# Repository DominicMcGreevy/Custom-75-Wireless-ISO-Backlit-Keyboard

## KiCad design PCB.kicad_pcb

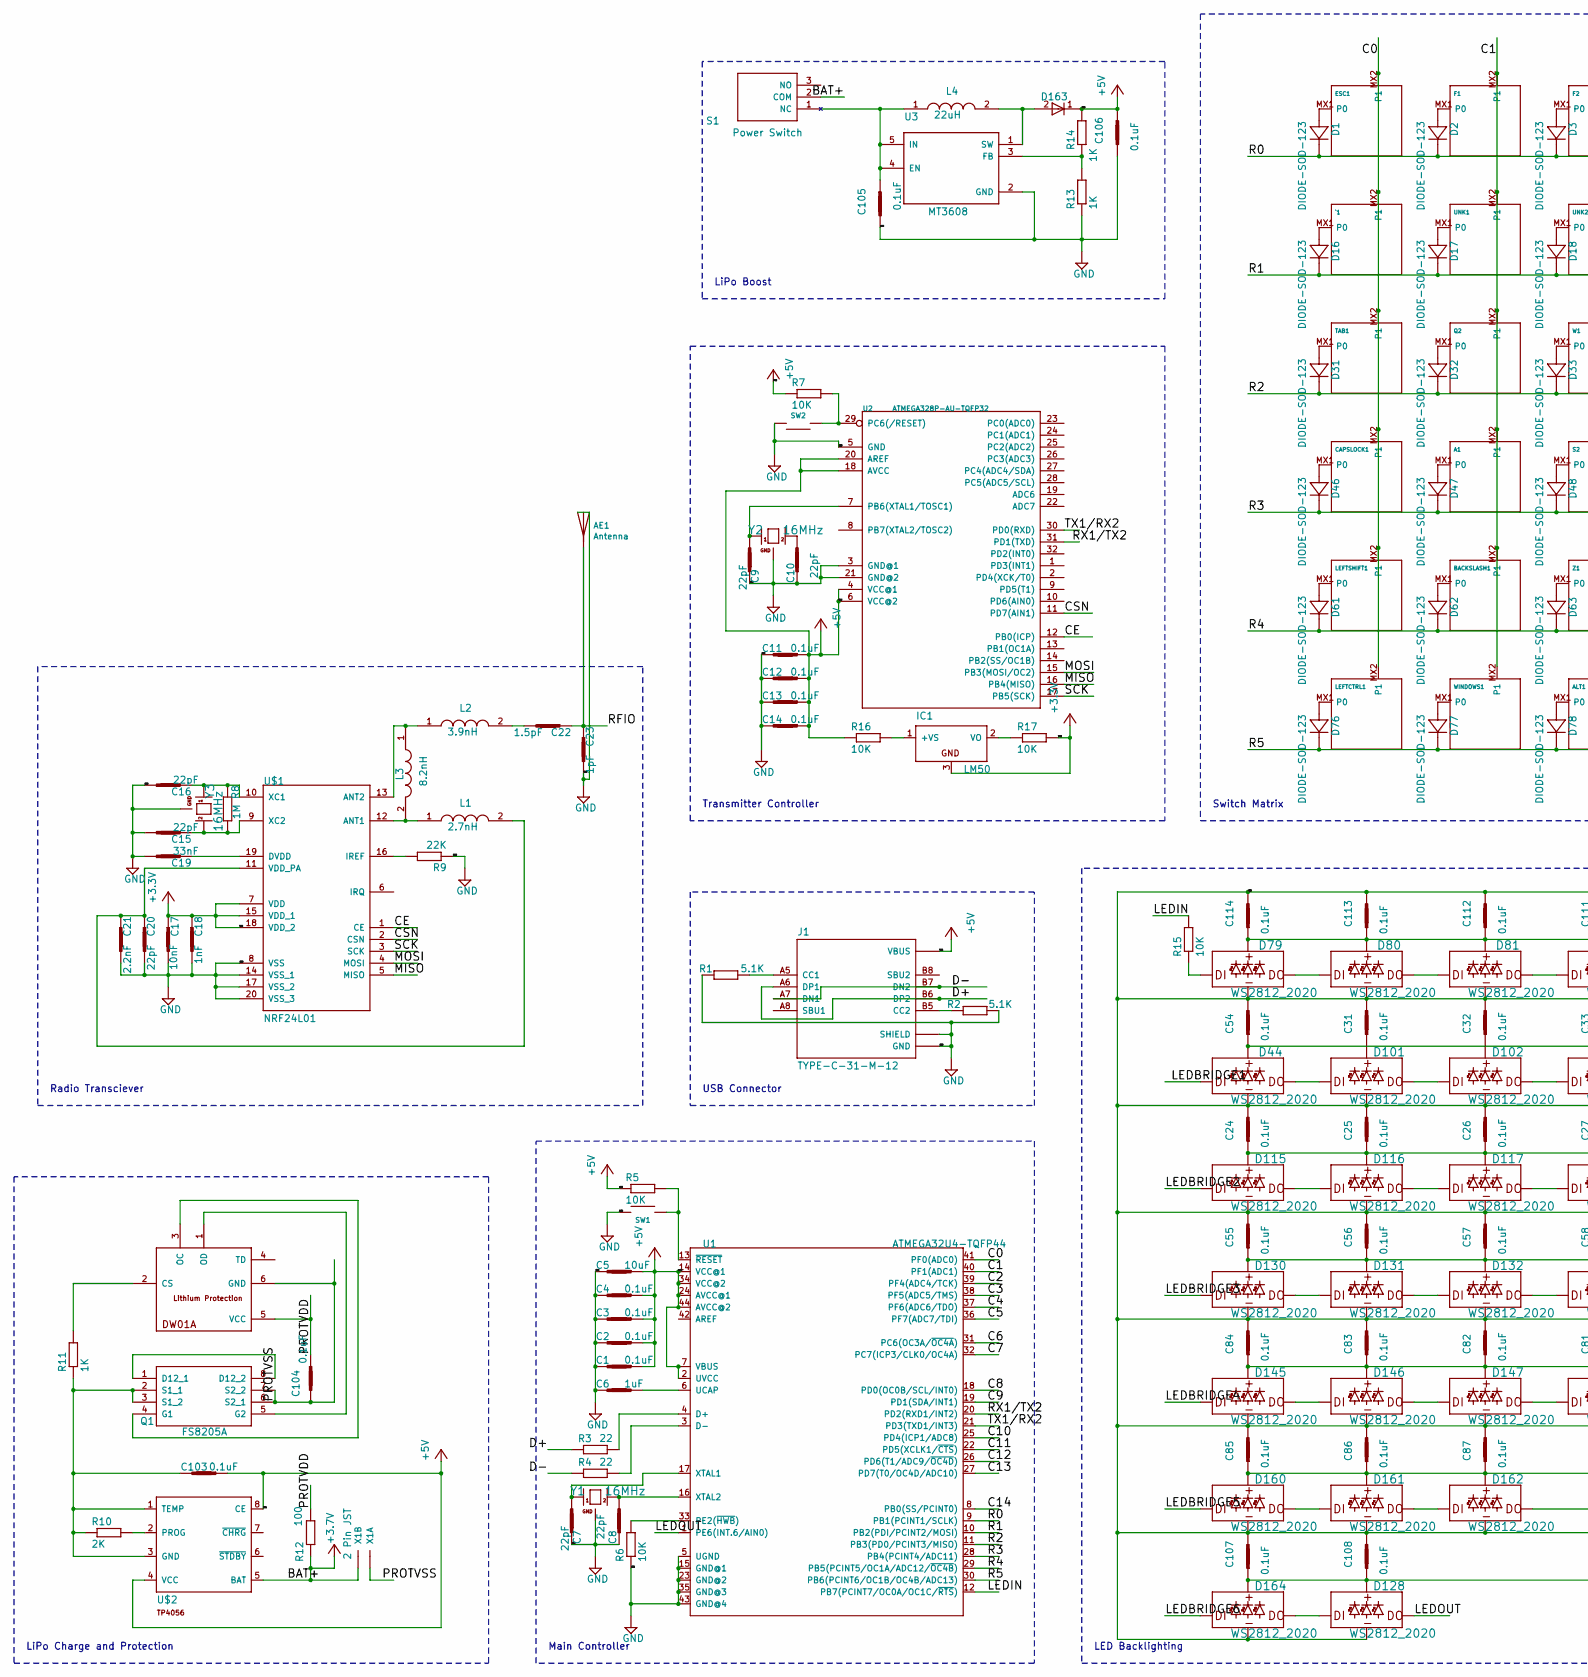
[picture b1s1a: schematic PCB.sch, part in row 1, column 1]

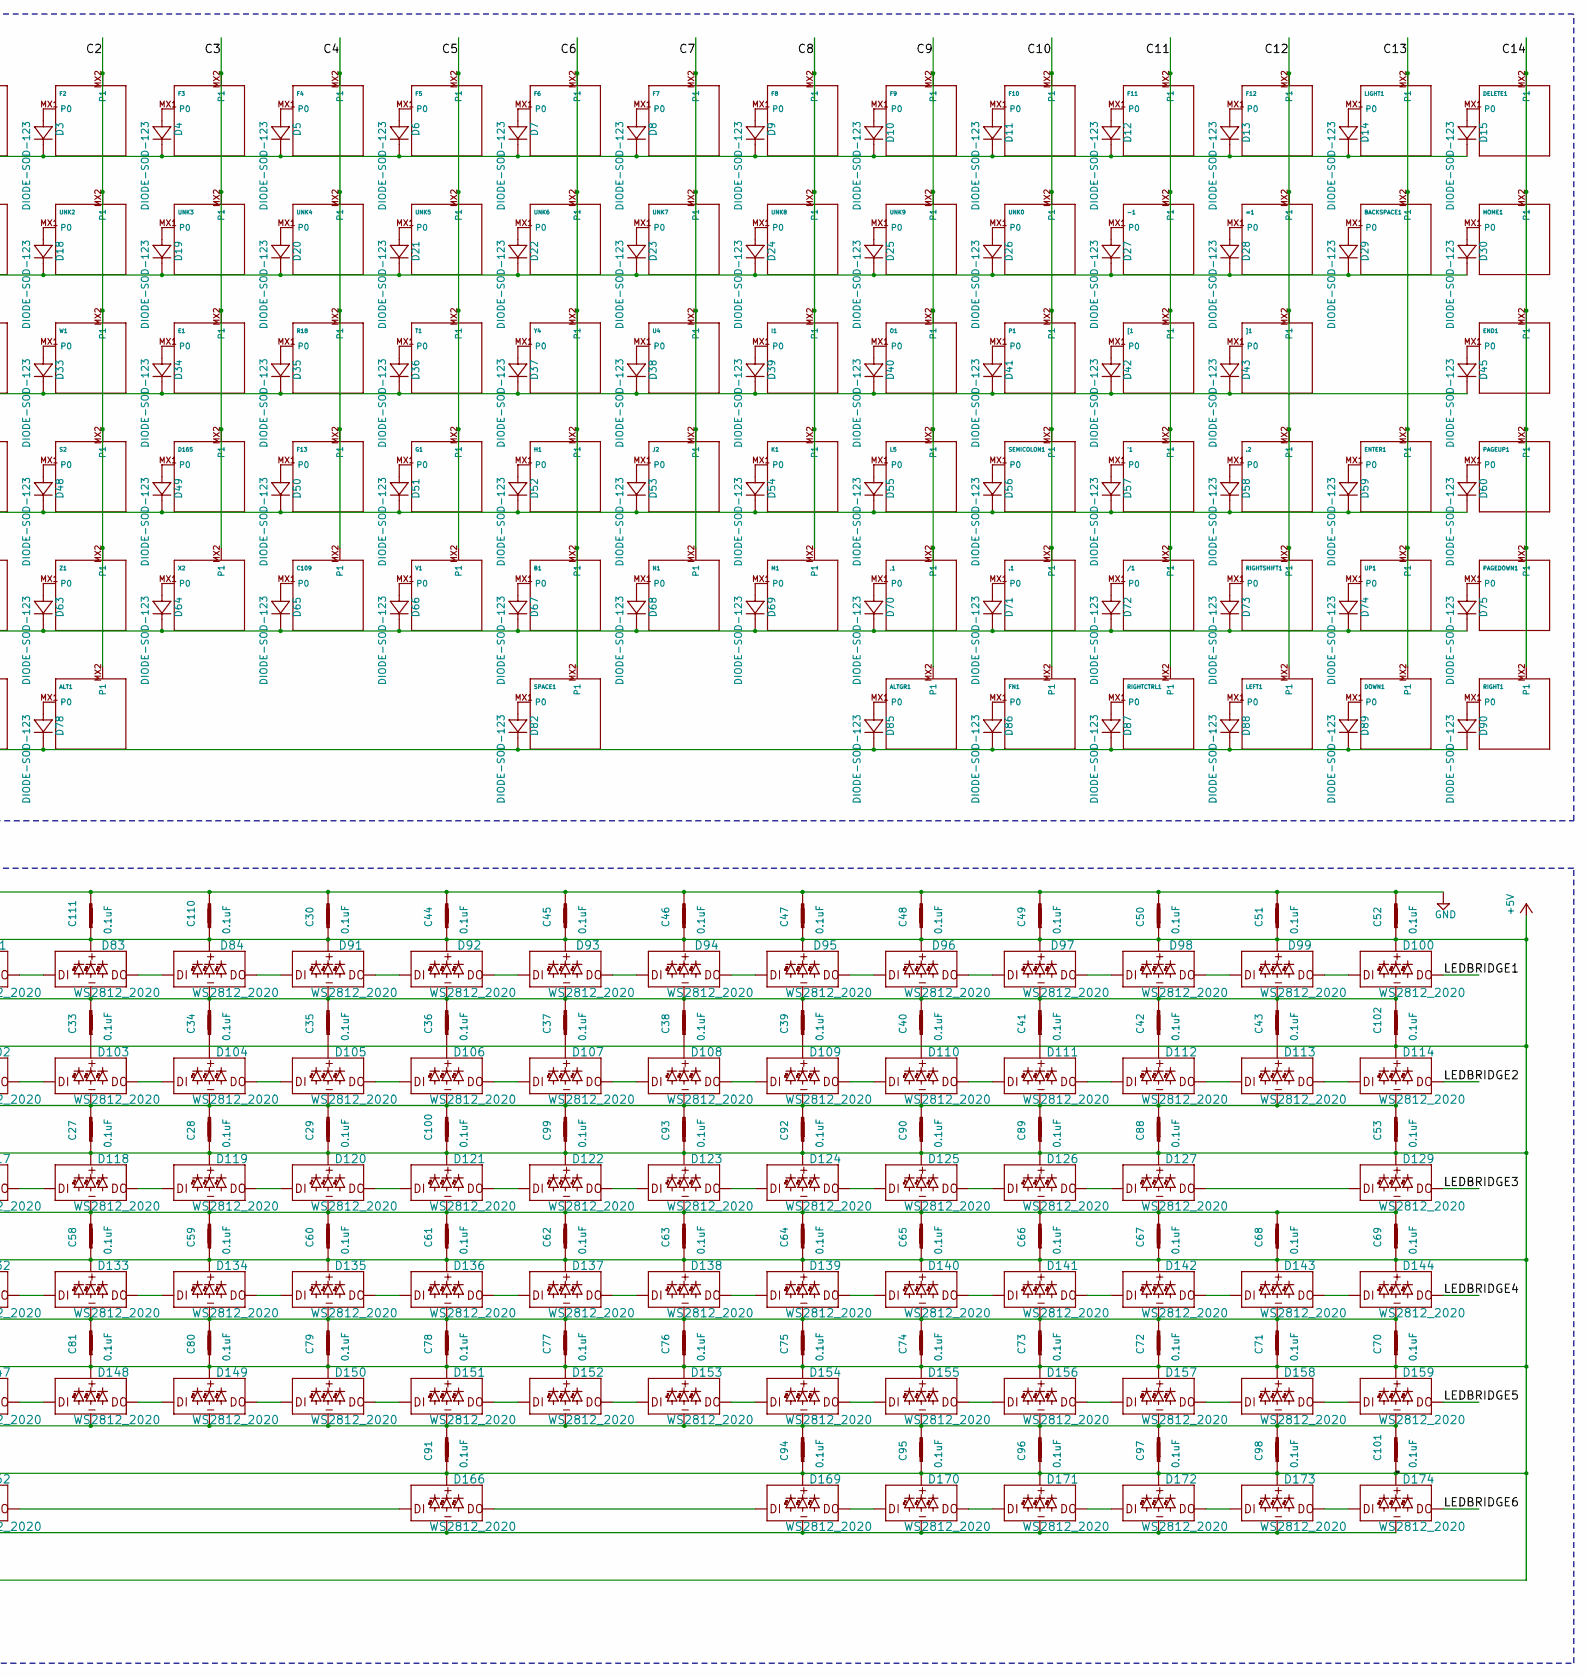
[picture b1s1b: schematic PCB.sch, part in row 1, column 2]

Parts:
'1: KEYSWITCH-PLAIN-MX-1U; MX-1U
,1: KEYSWITCH-PLAIN-MX-1U; MX-1U
-1: KEYSWITCH-PLAIN-MX-1U; MX-1U
.1, .2: KEYSWITCH-PLAIN-MX-1U; MX-1U
/1: KEYSWITCH-PLAIN-MX-1U; MX-1U
=1: KEYSWITCH-PLAIN-MX-1U; MX-1U
A1: KEYSWITCH-PLAIN-MX-1U; MX-1U
AE1: Antenna; Texas_SWRA117D_2.4GHz_Right
ALT1: KEYSWITCH-PLAIN-MX-1U; MX-1U
ALTGR1: KEYSWITCH-PLAIN-MX-1U; MX-1U
B1: KEYSWITCH-PLAIN-MX-1U; MX-1U
BACKSLASH1: KEYSWITCH-PLAIN-MX-1U; MX-1U
BACKSPACE1: KEYSWITCH-PLAIN-MX-2U-FLIPPED; MX-2U-FLIPPED
C1, C2, C3, C4, C11, C12, C13, C14, C24, C25, C26, C27, C28, C29, C30, C31, C32, C33, C34, C35, C36, C37, C38, C39, C40, C41, C42, C43, C44, C45, C46, C47, C48, C49, C50, C51, C52, C53, C54, C55, C56, C57, C58, C59, C60, C61, C62, C63, C64, C65, C66, C67, C68, C69, C70, C71, C72, C73, C74, C75, C76, C77, C78, C79, C80, C81, C82, C83, C84, C85, C86, C87, C88, C89, C90, C91, C92, C93, C94, C95, C96, C97, C98, C99, C100, C101, C102, C103, C104, C105, C106, C107, C108, C110, C111, C112, C113, C114: 0.1uF; C0805
C5: 10uF; C0805
C6: 1uF; C0805
C7, C8, C9, C10, C15, C16, C20: 22pF; C0805
C17: 10nF; C0805
C18: 1nF; C0805
C19: 33nF; C0805
C21: 2.2nF; C0805
C22: 1.5pF; C0805
C23: 1pF; C0805
C109: KEYSWITCH-PLAIN-MX-1U; MX-1U
CAPSLOCK1: KEYSWITCH-PLAIN-MX-1U; MX-1U
D1, D2, D3, D4, D5, D6, D7, D8, D9, D10, D11, D12, D13, D14, D15, D16, D17, D18, D19, D20, D21, D22, D23, D24, D25, D26, D27, D28, D29, D30, D31, D32, D33, D34, D35, D36, D37, D38, D39, D40, D41, D42, D43, D45, D46, D47, D48, D49, D50, D51, D52, D53, D54, D55, D56, D57, D58, D59, D60, D61, D62, D63, D64, D65, D66, D67, D68, D69, D70, D71, D72, D73, D74, D75, D76, D77, D78, D82, D85, D86, D87, D88, D89, D90: DIODE-SOD-123; SOD-123
D44, D79, D80, D81, D83, D84, D91, D92, D93, D94, D95, D96, D97, D98, D99, D100, D101, D102, D103, D104, D105, D106, D107, D108, D109, D110, D111, D112, D113, D114, D115, D116, D117, D118, D119, D120, D121, D122, D123, D124, D125, D126, D127, D128, D129, D130, D131, D132, D133, D134, D135, D136, D137, D138, D139, D140, D141, D142, D143, D144, D145, D146, D147, D148, D149, D150, D151, D152, D153, D154, D155, D156, D157, D158, D159, D160, D161, D162, D164, D166, D169, D170, D171, D172, D173, D174: WS2812_2020; WS2812-2020
D163: ES1D; DIOM5027-221N
D165: KEYSWITCH-PLAIN-MX-1U; MX-1U
DELETE1: KEYSWITCH-PLAIN-MX-1U; MX-1U
DOWN1: KEYSWITCH-PLAIN-MX-1U; MX-1U
E1: KEYSWITCH-PLAIN-MX-1U; MX-1U
END1: KEYSWITCH-PLAIN-MX-1U; MX-1U
ENTER1: KEYSWITCH-PLAIN-MX-2U-FLIPPED-ROTATED; MX-2U-FLIPPED-ROTATED
ESC1: KEYSWITCH-PLAIN-MX-1U; MX-1U
F1, F2, F3, F4, F5, F6, F7, F8, F9, F10, F11, F12, F13: KEYSWITCH-PLAIN-MX-1U; MX-1U
FN1: KEYSWITCH-PLAIN-MX-1U; MX-1U
G1: KEYSWITCH-PLAIN-MX-1U; MX-1U
H1: KEYSWITCH-PLAIN-MX-1U; MX-1U
HOME1: KEYSWITCH-PLAIN-MX-1U; MX-1U
I1: KEYSWITCH-PLAIN-MX-1U; MX-1U
IC1: LM50; SOT23
J1: TYPE-C-31-M-12; HRO_TYPE-C-31-M-12
J2: KEYSWITCH-PLAIN-MX-1U; MX-1U
K1: KEYSWITCH-PLAIN-MX-1U; MX-1U
L1: 2.7nH; LQW2BAN11NG00L
L2: 3.9nH; LQW18AS10NG0CD
L3: 8.2nH; LQW2BAN11NG00L
L4: 22uH; 7447706220
L5: KEYSWITCH-PLAIN-MX-1U; MX-1U
LEFT1: KEYSWITCH-PLAIN-MX-1U; MX-1U
LEFTCTRL1: KEYSWITCH-PLAIN-MX-1U; MX-1U
LEFTSHIFT1: KEYSWITCH-PLAIN-MX-1U; MX-1U
LIGHT1: KEYSWITCH-PLAIN-MX-1U; MX-1U
M1: KEYSWITCH-PLAIN-MX-1U; MX-1U
N1: KEYSWITCH-PLAIN-MX-1U; MX-1U
O1: KEYSWITCH-PLAIN-MX-1U; MX-1U
P1: KEYSWITCH-PLAIN-MX-1U; MX-1U
PAGEDOWN1: KEYSWITCH-PLAIN-MX-1U; MX-1U
PAGEUP1: KEYSWITCH-PLAIN-MX-1U; MX-1U
Q1: FS8205A; SOP65P640X120-8N
Q2: KEYSWITCH-PLAIN-MX-1U; MX-1U
R1, R2: 5.1K; R0805
R3, R4: 22; R0805
R5, R6, R7, R15, R16, R17: 10K; R0805
R8: 1M; R0805
R9: 22K; R0805
R10: 2K; R0805
R11, R13, R14: 1K; R0805
R12: 100; R0805
R18: KEYSWITCH-PLAIN-MX-1U; MX-1U
RIGHT1: KEYSWITCH-PLAIN-MX-1U; MX-1U
RIGHTCTRL1: KEYSWITCH-PLAIN-MX-1U; MX-1U
RIGHTSHIFT1: KEYSWITCH-PLAIN-MX-1U; MX-1U
S1: Power Switch; MINISPDTSW
S2: KEYSWITCH-PLAIN-MX-1U; MX-1U
SEMICOLON1: KEYSWITCH-PLAIN-MX-1U; MX-1U
SPACE1: KEYSWITCH-PLAIN-MX-6.25U-FLIPPED; MX-6.25U-FLIPPED
SW1, SW2: SWITCH-SMD-EVP-BB2A9B00
T1: KEYSWITCH-PLAIN-MX-1U; MX-1U
TAB1: KEYSWITCH-PLAIN-MX-1U; MX-1U
U1: ATMEGA32U4-TQFP44; TQFP44-0.8-9.6X9.6MM
U2: ATMEGA328P-AU-TQFP32; TQFP32-0.8-7X7MM
U3: MT3608; SOT95P280X145-6N
U4: KEYSWITCH-PLAIN-MX-1U; MX-1U
U$1: NRF24L01; QFN20
U$2: TP4056; SOT23-8
U$3: DW01A; SOT23-6
UNK0, UNK1, UNK2, UNK3, UNK4, UNK5, UNK6, UNK7, UNK8, UNK9: KEYSWITCH-PLAIN-MX-1U; MX-1U
UP1: KEYSWITCH-PLAIN-MX-1U; MX-1U
V1: KEYSWITCH-PLAIN-MX-1U; MX-1U
W1: KEYSWITCH-PLAIN-MX-1U; MX-1U
WINDOWS1: KEYSWITCH-PLAIN-MX-1U; MX-1U
X1: 2 Pin JST; JST-XH-02-PACKAGE-LONG-PAD
X2: KEYSWITCH-PLAIN-MX-1U; MX-1U
Y1, Y2, Y3: 16MHz; CRYSTAL-3.2X2.5
Y4: KEYSWITCH-PLAIN-MX-1U; MX-1U
Z1: KEYSWITCH-PLAIN-MX-1U; MX-1U
[1: KEYSWITCH-PLAIN-MX-1U; MX-1U
]1: KEYSWITCH-PLAIN-MX-1U; MX-1U
`1: KEYSWITCH-PLAIN-MX-1U; MX-1U

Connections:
/C0: CAPSLOCK1.MX2 (P1), ESC1.MX2 (P1), LEFTCTRL1.MX2 (P1), LEFTSHIFT1.MX2 (P1), TAB1.MX2 (P1), U1.41 (PF0(ADC0)), `1.MX2 (P1)
/C1: A1.MX2 (P1), BACKSLASH1.MX2 (P1), F1.MX2 (P1), Q2.MX2 (P1), U1.40 (PF1(ADC1)), UNK1.MX2 (P1), WINDOWS1.MX2 (P1)
/C2: ALT1.MX2 (P1), F2.MX2 (P1), S2.MX2 (P1), U1.39 (PF4(ADC4/TCK)), UNK2.MX2 (P1), W1.MX2 (P1), Z1.MX2 (P1)
/C3: D165.MX2 (P1), E1.MX2 (P1), F3.MX2 (P1), U1.38 (PF5(ADC5/TMS)), UNK3.MX2 (P1), X2.MX2 (P1)
/C4: C109.MX2 (P1), F4.MX2 (P1), F13.MX2 (P1), R18.MX2 (P1), U1.37 (PF6(ADC6/TDO)), UNK4.MX2 (P1)
/C5: F5.MX2 (P1), G1.MX2 (P1), T1.MX2 (P1), U1.36 (PF7(ADC7/TDI)), UNK5.MX2 (P1), V1.MX2 (P1)
/C6: B1.MX2 (P1), F6.MX2 (P1), H1.MX2 (P1), SPACE1.MX2 (P1), U1.31 (PC6(OC3A/~OC4A)), UNK6.MX2 (P1), Y4.MX2 (P1)
/C7: F7.MX2 (P1), J2.MX2 (P1), N1.MX2 (P1), U1.32 (PC7(ICP3/CLK0/OC4A)), U4.MX2 (P1), UNK7.MX2 (P1)
/C8: F8.MX2 (P1), I1.MX2 (P1), K1.MX2 (P1), M1.MX2 (P1), U1.18 (PD0(OC0B/SCL/INT0)), UNK8.MX2 (P1)
/C9: ,1.MX2 (P1), ALTGR1.MX2 (P1), F9.MX2 (P1), L5.MX2 (P1), O1.MX2 (P1), U1.19 (PD1(SDA/INT1)), UNK9.MX2 (P1)
/C10: .1.MX2 (P1), F10.MX2 (P1), FN1.MX2 (P1), P1.MX2 (P1), SEMICOLON1.MX2 (P1), U1.25 (PD4(ICP1/ADC8)), UNK0.MX2 (P1)
/C11: '1.MX2 (P1), -1.MX2 (P1), /1.MX2 (P1), F11.MX2 (P1), RIGHTCTRL1.MX2 (P1), U1.22 (PD5(XCLK1/~CTS)), [1.MX2 (P1)
/C12: .2.MX2 (P1), =1.MX2 (P1), F12.MX2 (P1), LEFT1.MX2 (P1), RIGHTSHIFT1.MX2 (P1), U1.26 (PD6(T1/ADC9/~OC4D)), ]1.MX2 (P1)
/C13: BACKSPACE1.MX2 (P1), DOWN1.MX2 (P1), ENTER1.MX2 (P1), LIGHT1.MX2 (P1), U1.27 (PD7(T0/OC4D/ADC10)), UP1.MX2 (P1)
/C14: DELETE1.MX2 (P1), END1.MX2 (P1), HOME1.MX2 (P1), PAGEDOWN1.MX2 (P1), PAGEUP1.MX2 (P1), RIGHT1.MX2 (P1), U1.8 (PB0(SS/PCINT0))
/CE: U2.12 (PB0(ICP)), U$1.1 (CE)
/CSN: U2.11 (PD7(AIN1)), U$1.2 (CSN)
/D+: J1.A6 (DP1), J1.B6 (DP2), R3.2
/D-: J1.A7 (DN1), J1.B7 (DN2), R4.2
/LEDBRIDGE1: D44.DI, D100.DO
/LEDBRIDGE2: D114.DO, D115.DI
/LEDBRIDGE3: D129.DO, D130.DI
/LEDBRIDGE4: D144.DO, D145.DI
/LEDBRIDGE5: D159.DO, D160.DI
/LEDBRIDGE6: D164.DI, D174.DO
/LEDIN: R15.2, U1.12 (PB7(PCINT7/OC0A/OC1C/~RTS))
/LEDOUT: D128.DO, U1.1 (PE6(INT.6/AIN0))
/MISO: U2.16 (PB4(MISO)), U$1.5 (MISO)
/MOSI: U2.15 (PB3(MOSI/OC2)), U$1.4 (MOSI)
/PROTVDD: C104.1, R12.2, U$3.5 (VCC)
/PROTVSS: C104.2, Q1.6 (S2_1), Q1.7 (S2_2), U$3.6 (GND), X1.2
/R0: D1.C, D2.C, D3.C, D4.C, D5.C, D6.C, D7.C, D8.C, D9.C, D10.C, D11.C, D12.C, D13.C, D14.C, D15.C, U1.9 (PB1(PCINT1/SCLK))
/R1: D16.C, D17.C, D18.C, D19.C, D20.C, D21.C, D22.C, D23.C, D24.C, D25.C, D26.C, D27.C, D28.C, D29.C, D30.C, U1.10 (PB2(PDI/PCINT2/MOSI))
/R2: D31.C, D32.C, D33.C, D34.C, D35.C, D36.C, D37.C, D38.C, D39.C, D40.C, D41.C, D42.C, D43.C, D45.C, U1.11 (PB3(PD0/PCINT3/MISO))
/R3: D46.C, D47.C, D48.C, D49.C, D50.C, D51.C, D52.C, D53.C, D54.C, D55.C, D56.C, D57.C, D58.C, D59.C, D60.C, U1.28 (PB4(PCINT4/ADC11))
/R4: D61.C, D62.C, D63.C, D64.C, D65.C, D66.C, D67.C, D68.C, D69.C, D70.C, D71.C, D72.C, D73.C, D74.C, D75.C, U1.29 (PB5(PCINT5/OC1A/ADC12/~OC4B))
/R5: D76.C, D77.C, D78.C, D82.C, D85.C, D86.C, D87.C, D88.C, D89.C, D90.C, U1.30 (PB6(PCINT6/OC1B/OC4B/ADC13))
/RFIO: AE1.1, C22.1, C23.1
/RX1/TX2: U1.20 (PD2(RXD1/INT2)), U2.31 (PD1(TXD))
/SCK: U2.17 (PB5(SCK)), U$1.3 (SCK)
/TX1/RX2: U1.21 (PD3(TXD1/INT3)), U2.30 (PD0(RXD))
GND: C1.2, C2.2, C3.2, C4.2, C5.2, C6.1, C7.1, C8.1, C9.1, C10.1, C11.2, C12.2, C13.2, C14.2, C15.2, C16.2, C17.2, C18.2, C19.2, C20.2, C21.2, C23.2, C24.2, C25.2, C26.2, C27.2, C28.2, C29.2, C30.2, C31.2, C32.2, C33.2, C34.2, C35.2, C36.2, C37.2, C38.2, C39.2, C40.2, C41.2, C42.2, C43.2, C44.2, C45.2, C46.2, C47.2, C48.2, C49.2, C50.2, C51.2, C52.2, C53.2, C54.2, C55.2, C56.2, C57.2, C58.2, C59.2, C60.2, C61.2, C62.2, C63.2, C64.2, C65.2, C66.2, C67.2, C68.2, C69.2, C70.2, C71.2, C72.2, C73.2, C74.2, C75.2, C76.2, C77.2, C78.2, C79.2, C80.2, C81.2, C82.2, C83.2, C84.2, C85.2, C86.2, C87.2, C88.2, C89.2, C90.2, C91.2, C92.2, C93.2, C94.2, C95.2, C96.2, C97.2, C98.2, C99.2, C100.2, C101.2, C102.2, C105.2, C106.2, C107.2, C108.2, C110.2, C111.2, C112.2, C113.2, C114.2, D44.GND, D79.GND, D80.GND, D81.GND, D83.GND, D84.GND, D91.GND, D92.GND, D93.GND, D94.GND, D95.GND, D96.GND, D97.GND, D98.GND, D99.GND, D100.GND, D101.GND, D102.GND, D103.GND, D104.GND, D105.GND, D106.GND, D107.GND, D108.GND, D109.GND, D110.GND, D111.GND, D112.GND, D113.GND, D114.GND, D115.GND, D116.GND, D117.GND, D118.GND, D119.GND, D120.GND, D121.GND, D122.GND, D123.GND, D124.GND, D125.GND, D126.GND, D127.GND, D128.GND, D129.GND, D130.GND, D131.GND, D132.GND, D133.GND, D134.GND, D135.GND, D136.GND, D137.GND, D138.GND, D139.GND, D140.GND, D141.GND, D142.GND, D143.GND, D144.GND, D145.GND, D146.GND, D147.GND, D148.GND, D149.GND, D150.GND, D151.GND, D152.GND, D153.GND, D154.GND, D155.GND, D156.GND, D157.GND, D158.GND, D159.GND, D160.GND, D161.GND, D162.GND, D164.GND, D166.GND, D169.GND, D170.GND, D171.GND, D172.GND, D173.GND, D174.GND, J1.A1B12 (GND), J1.B1A12 (GND), J1.S1 (SHIELD), J1.S2 (SHIELD), J1.S3 (SHIELD), J1.S4 (SHIELD), R1.1, R2.2, R6.1, R9.1, R13.1, SW1.A@1 (1), SW1.A@2 (1), SW2.B@3 (2), SW2.B@4 (2), U1.5 (UGND), U1.15 (GND@1), U1.23 (GND@2), U1.35 (GND@3), U1.43 (GND@4), U2.3 (GND@1), U2.5 (GND), U2.21 (GND@2), U3.2 (GND), U$1.8 (VSS), U$1.14 (VSS_1), U$1.17 (VSS_2), U$1.20 (VSS_3), Y1.2 (GND), Y1.4 (GND), Y2.2 (GND), Y2.4 (GND), Y3.2 (GND), Y3.4 (GND)
unnamed: '1.MX1 (P0), D57.A
unnamed: ,1.MX1 (P0), D70.A
unnamed: -1.MX1 (P0), D27.A
unnamed: .1.MX1 (P0), D71.A
unnamed: .2.MX1 (P0), D58.A
unnamed: /1.MX1 (P0), D72.A
unnamed: =1.MX1 (P0), D28.A
unnamed: A1.MX1 (P0), D47.A
unnamed: ALT1.MX1 (P0), D78.A
unnamed: ALTGR1.MX1 (P0), D85.A
unnamed: B1.MX1 (P0), D67.A
unnamed: BACKSLASH1.MX1 (P0), D62.A
unnamed: BACKSPACE1.MX1 (P0), D29.A
unnamed: C6.2, U1.6 (UCAP)
unnamed: C7.2, U1.17 (XTAL1), Y1.1
unnamed: C8.2, U1.16 (XTAL2), Y1.3 (2)
unnamed: C9.2, U2.7 (PB6(XTAL1/TOSC1)), Y2.1
unnamed: C10.2, Y2.3 (2)
unnamed: C15.1, R8.1, U$1.9 (XC2), Y3.3 (2)
unnamed: C16.1, R8.2, U$1.10 (XC1), Y3.1
unnamed: C19.1, U$1.19 (DVDD)
unnamed: C20.1, C21.1, L1.2, U$1.11 (VDD_PA)
unnamed: C22.2, L2.2
unnamed: C31.1, D101.VCC
unnamed: C32.1, D102.VCC
unnamed: C33.1, D103.VCC
unnamed: C34.1, D104.VCC
unnamed: C35.1, D105.VCC
unnamed: C36.1, D106.VCC
unnamed: C37.1, D107.VCC
unnamed: C38.1, D108.VCC
unnamed: C39.1, D109.VCC
unnamed: C40.1, D110.VCC
unnamed: C41.1, D111.VCC
unnamed: C42.1, D112.VCC
unnamed: C43.1, D113.VCC
unnamed: C103.2, Q1.2 (S1_1), Q1.3 (S1_2), R10.1, R11.1, U$2.1 (TEMP), U$2.3 (GND)
unnamed: C105.1, L4.1, S1.1 (NC), U3.4 (EN), U3.5 (IN)
unnamed: C109.MX1 (P0), D65.A
unnamed: CAPSLOCK1.MX1 (P0), D46.A
unnamed: D1.A, ESC1.MX1 (P0)
unnamed: D2.A, F1.MX1 (P0)
unnamed: D3.A, F2.MX1 (P0)
unnamed: D4.A, F3.MX1 (P0)
unnamed: D5.A, F4.MX1 (P0)
unnamed: D6.A, F5.MX1 (P0)
unnamed: D7.A, F6.MX1 (P0)
unnamed: D8.A, F7.MX1 (P0)
unnamed: D9.A, F8.MX1 (P0)
unnamed: D10.A, F9.MX1 (P0)
unnamed: D11.A, F10.MX1 (P0)
unnamed: D12.A, F11.MX1 (P0)
unnamed: D13.A, F12.MX1 (P0)
unnamed: D14.A, LIGHT1.MX1 (P0)
unnamed: D15.A, DELETE1.MX1 (P0)
unnamed: D16.A, `1.MX1 (P0)
unnamed: D17.A, UNK1.MX1 (P0)
unnamed: D18.A, UNK2.MX1 (P0)
unnamed: D19.A, UNK3.MX1 (P0)
unnamed: D20.A, UNK4.MX1 (P0)
unnamed: D21.A, UNK5.MX1 (P0)
unnamed: D22.A, UNK6.MX1 (P0)
unnamed: D23.A, UNK7.MX1 (P0)
unnamed: D24.A, UNK8.MX1 (P0)
unnamed: D25.A, UNK9.MX1 (P0)
unnamed: D26.A, UNK0.MX1 (P0)
unnamed: D30.A, HOME1.MX1 (P0)
unnamed: D31.A, TAB1.MX1 (P0)
unnamed: D32.A, Q2.MX1 (P0)
unnamed: D33.A, W1.MX1 (P0)
unnamed: D34.A, E1.MX1 (P0)
unnamed: D35.A, R18.MX1 (P0)
unnamed: D36.A, T1.MX1 (P0)
unnamed: D37.A, Y4.MX1 (P0)
unnamed: D38.A, U4.MX1 (P0)
unnamed: D39.A, I1.MX1 (P0)
unnamed: D40.A, O1.MX1 (P0)
unnamed: D41.A, P1.MX1 (P0)
unnamed: D42.A, [1.MX1 (P0)
unnamed: D43.A, ]1.MX1 (P0)
unnamed: D45.A, END1.MX1 (P0)
unnamed: D48.A, S2.MX1 (P0)
unnamed: D50.A, F13.MX1 (P0)
unnamed: D51.A, G1.MX1 (P0)
unnamed: D52.A, H1.MX1 (P0)
unnamed: D53.A, J2.MX1 (P0)
unnamed: D54.A, K1.MX1 (P0)
unnamed: D55.A, L5.MX1 (P0)
unnamed: D56.A, SEMICOLON1.MX1 (P0)
unnamed: D59.A, ENTER1.MX1 (P0)
unnamed: D60.A, PAGEUP1.MX1 (P0)
unnamed: D61.A, LEFTSHIFT1.MX1 (P0)
unnamed: D63.A, Z1.MX1 (P0)
unnamed: D64.A, X2.MX1 (P0)
unnamed: D66.A, V1.MX1 (P0)
unnamed: D68.A, N1.MX1 (P0)
unnamed: D69.A, M1.MX1 (P0)
unnamed: D73.A, RIGHTSHIFT1.MX1 (P0)
unnamed: D74.A, UP1.MX1 (P0)
unnamed: D75.A, PAGEDOWN1.MX1 (P0)
unnamed: D76.A, LEFTCTRL1.MX1 (P0)
unnamed: D77.A, WINDOWS1.MX1 (P0)
unnamed: D79.DI, R15.1
unnamed: D79.DO, D80.DI
unnamed: D80.DO, D81.DI
unnamed: D81.DO, D83.DI
unnamed: D82.A, SPACE1.MX1 (P0)
unnamed: D83.DO, D84.DI
unnamed: D84.DO, D91.DI
unnamed: D86.A, FN1.MX1 (P0)
unnamed: D87.A, RIGHTCTRL1.MX1 (P0)
unnamed: D88.A, LEFT1.MX1 (P0)
unnamed: D89.A, DOWN1.MX1 (P0)
unnamed: D90.A, RIGHT1.MX1 (P0)
unnamed: D91.DO, D92.DI
unnamed: D92.DO, D93.DI
unnamed: D93.DO, D94.DI
unnamed: D94.DO, D95.DI
unnamed: D95.DO, D96.DI
unnamed: D96.DO, D97.DI
unnamed: D97.DO, D98.DI
unnamed: D98.DO, D99.DI
unnamed: D99.DO, D100.DI
unnamed: D44.DO, D101.DI
unnamed: D101.DO, D102.DI
unnamed: D102.DO, D103.DI
unnamed: D103.DO, D104.DI
unnamed: D104.DO, D105.DI
unnamed: D105.DO, D106.DI
unnamed: D106.DO, D107.DI
unnamed: D107.DO, D108.DI
unnamed: D108.DO, D109.DI
unnamed: D109.DO, D110.DI
unnamed: D110.DO, D111.DI
unnamed: D111.DO, D112.DI
unnamed: D112.DO, D113.DI
unnamed: D113.DO, D114.DI
unnamed: D115.DO, D116.DI
unnamed: D116.DO, D117.DI
unnamed: D117.DO, D118.DI
unnamed: D118.DO, D119.DI
unnamed: D119.DO, D120.DI
unnamed: D120.DO, D121.DI
unnamed: D121.DO, D122.DI
unnamed: D122.DO, D123.DI
unnamed: D123.DO, D124.DI
unnamed: D124.DO, D125.DI
unnamed: D125.DO, D126.DI
unnamed: D126.DO, D127.DI
unnamed: D127.DO, D129.DI
unnamed: D128.DI, D164.DO
unnamed: D130.DO, D131.DI
unnamed: D131.DO, D132.DI
unnamed: D132.DO, D133.DI
unnamed: D133.DO, D134.DI
unnamed: D134.DO, D135.DI
unnamed: D135.DO, D136.DI
unnamed: D136.DO, D137.DI
unnamed: D137.DO, D138.DI
unnamed: D138.DO, D139.DI
unnamed: D139.DO, D140.DI
unnamed: D140.DO, D141.DI
unnamed: D141.DO, D142.DI
unnamed: D142.DO, D143.DI
unnamed: D143.DO, D144.DI
unnamed: D145.DO, D146.DI
unnamed: D146.DO, D147.DI
unnamed: D147.DO, D148.DI
unnamed: D148.DO, D149.DI
unnamed: D149.DO, D150.DI
unnamed: D150.DO, D151.DI
unnamed: D151.DO, D152.DI
unnamed: D152.DO, D153.DI
unnamed: D153.DO, D154.DI
unnamed: D154.DO, D155.DI
unnamed: D155.DO, D156.DI
unnamed: D156.DO, D157.DI
unnamed: D157.DO, D158.DI
unnamed: D158.DO, D159.DI
unnamed: D160.DO, D161.DI
unnamed: D161.DO, D162.DI
unnamed: D162.DO, D166.DI
unnamed: D163.2 (A), L4.2, U3.1 (SW)
unnamed: D49.A, D165.MX1 (P0)
unnamed: D166.DO, D169.DI
unnamed: D169.DO, D170.DI
unnamed: D170.DO, D171.DI
unnamed: D171.DO, D172.DI
unnamed: D172.DO, D173.DI
unnamed: D173.DO, D174.DI
unnamed: IC1.1 (+VS), R16.2
unnamed: IC1.2 (VO), R17.1
unnamed: J1.A5 (CC1), R1.2
unnamed: J1.B5 (CC2), R2.1
unnamed: L1.1, L3.2, U$1.12 (ANT1)
unnamed: L2.1, L3.1, U$1.13 (ANT2)
unnamed: Q1.1 (D12_1), Q1.8 (D12_2)
unnamed: Q1.4 (G1), U$3.3 (OC)
unnamed: Q1.5 (G2), U$3.1 (OD)
unnamed: R3.1, U1.4 (D+)
unnamed: R4.1, U1.3 (D-)
unnamed: R5.2, SW1.B@3 (2), SW1.B@4 (2), U1.13 (~RESET)
unnamed: R6.2, U1.33 (PE2(~HWB))
unnamed: R7.2, SW2.A@1 (1), SW2.A@2 (1), U2.29 (PC6(/RESET))
unnamed: R9.2, U$1.16 (IREF)
unnamed: R10.2, U$2.2 (PROG)
unnamed: R11.2, U$3.2 (CS)
unnamed: R13.2, R14.1, U3.3 (FB)

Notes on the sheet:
USB Connector
Main Controller
Transmitter Controller
Switch Matrix
LED Backlighting
Radio Transciever
LiPo Charge and Protection
LiPo Boost

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
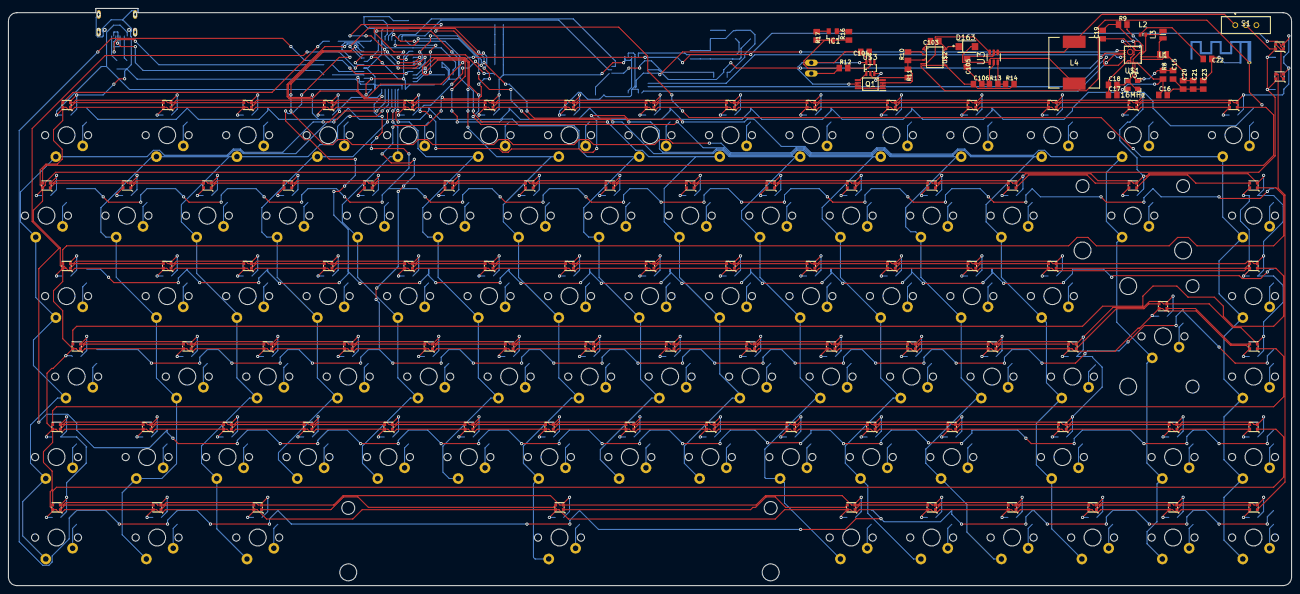
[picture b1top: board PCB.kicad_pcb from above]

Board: 2 copper layers, 303.8 x 136.6 mm, 406 parts (0 on the bottom side), 251 nets.
